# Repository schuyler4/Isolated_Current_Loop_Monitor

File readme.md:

<h1> Isolated Current Loop Monitor </h1>

<center>

</center>

<p> This circuit monitors the state of a switch (or many switches in series) with an isolated signal. This is the only way to truly monitor the state of a switch without any
information about the signal that the switch is switching. 
</p>
<h3>Inputs</h3>
<ul>
<li>12V Power</li>
<li>Switch Loop (Connect each end to switch connector)</li>
</ul>
<h3>Output</h3>
The output is open collector with a 10k pull up resistor. When the 
switch loop is closed, the open collector pulls low, and when the switch
is open, it releases.

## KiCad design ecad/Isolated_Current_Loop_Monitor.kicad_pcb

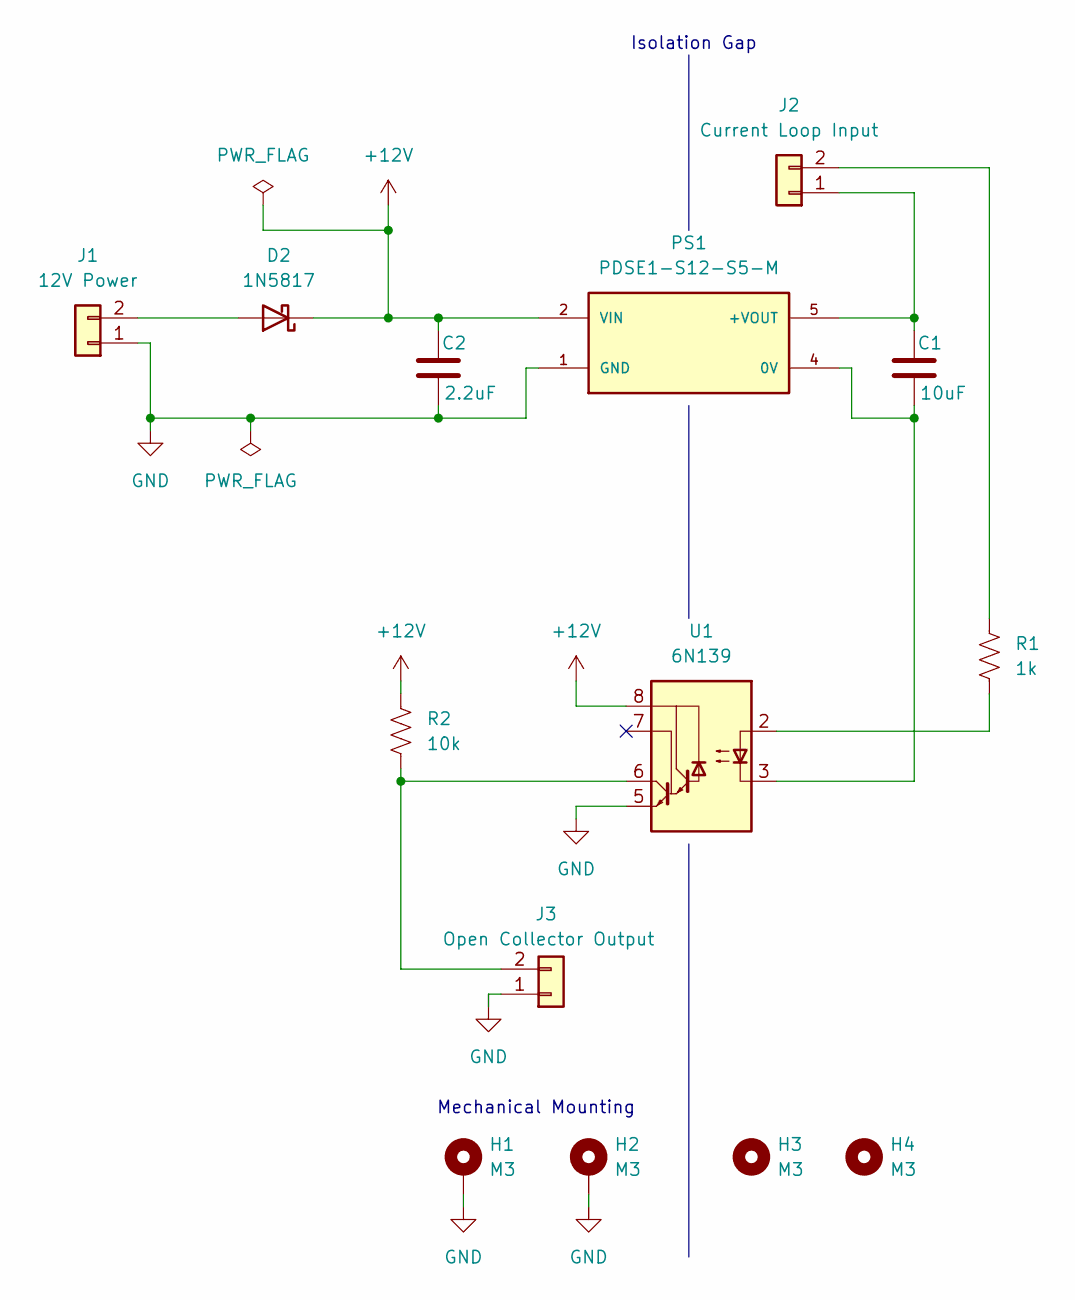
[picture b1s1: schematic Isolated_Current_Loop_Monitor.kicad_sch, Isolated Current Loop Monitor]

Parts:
C1: 10uF; C_Disc_D6.0mm_W2.5mm_P5.00mm; Part # FG20X7R1H106KRT06; Digikey Part # 445-173297-1-ND
C2: 2.2uF; C_Disc_D6.0mm_W2.5mm_P5.00mm; Part # RDER71H225K2M1H03A; Digikey Part # 490-9164-1-ND
D2: 1N5817; D_DO-41_SOD81_P10.16mm_Horizontal; Part # 1N5817; Digikey Part # 497-4547-1-ND
H1, H2: M3; MountingHole_3.2mm_M3_Pad_Via
H3, H4: M3; MountingHole_3.2mm_M3
J1: 12V Power; MOLEX_2125280200; Part # 2125280200; Digikey Part # 900-2125280200-ND
J2: Current Loop Input; MOLEX_2125280200; Part # 2125280200; Digikey Part # 900-2125280200-ND
J3: Open Collector Output; MOLEX_2125280200; Part # 2125280200; Digikey Part # 900-2125280200-ND
PS1: PDSE1-S12-S5-M; CONV_PDSE1-S12-S5-M; PARTREV 1.0; Digikey Part # 102-PDSE1-S12-S5-M-ND
R1: 1k; R_Axial_DIN0207_L6.3mm_D2.5mm_P7.62mm_Horizontal; Part # CFF14JT1K00; Digikey Part # 738-CFF14JT1K00CT-ND
R2: 10k; R_Axial_DIN0207_L6.3mm_D2.5mm_P7.62mm_Horizontal; Part # CF14JT10K0; Digikey Part # CF14JT10K0CT-ND
U1: 6N139; DIP-8_W7.62mm; Part # 6N139-ND; Digikey Part # 6N139-ND

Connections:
+12V: C2.1, D2.1 (K), PS1.2 (VIN), R2.1, U1.8 (VCC)
GND: C2.2, H1.1, H2.1, J1.1, J3.1, PS1.1 (GND), U1.5 (GND)
unnamed: D2.2 (A), J1.2
unnamed: C1.1, J2.1, PS1.5 (+VOUT)
unnamed: J2.2, R1.1
unnamed: J3.2, R2.2, U1.6 (VO2)
unnamed: C1.2, PS1.4 (0V), U1.3 (C2)
unnamed: R1.2, U1.2 (C1)

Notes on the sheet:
Isolation Gap
Mechanical Mounting

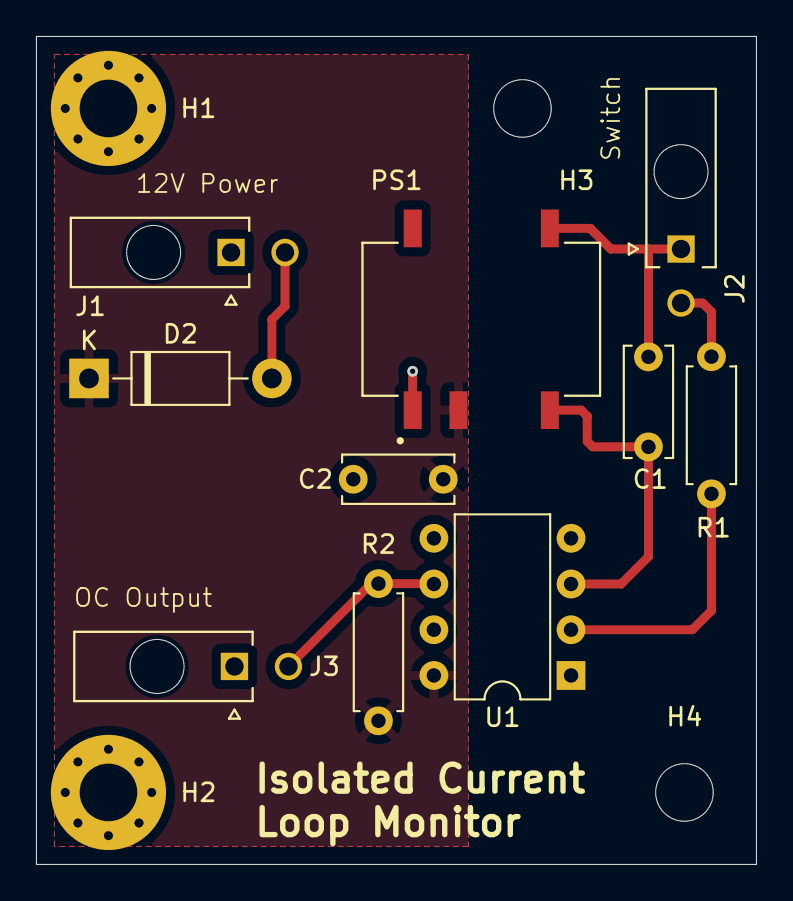
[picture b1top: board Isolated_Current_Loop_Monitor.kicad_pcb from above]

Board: 2 copper layers, 40.0 x 46.0 mm, 14 parts (0 on the bottom side), 8 nets.

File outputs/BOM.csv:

Reference,Value,Qty,Part #,Digikey Part #,Unit Price
C1,10uF,1,FG20X7R1H106KRT06,445-173297-1-ND,1.29
C2,2.2uF,1,RDER71H225K2M1H03A,490-9164-1-ND,0.74
D2,1N5817,1,1N5817,497-4547-1-ND,0.42
J1,12V Power,1,2125280200,900-2125280200-ND,2.13
J2,Current Loop Input,1,2125280200,900-2125280200-ND,2.13
J3,Open Collector Output,1,2125280200,900-2125280200-ND,2.13
PS1,PDSE1-S12-S5-M,1,PDSE1-S12-S5-M,102-PDSE1-S12-S5-M-ND,3.45
R1,1k,1,CFF14JT1K00,738-CFF14JT1K00CT-ND,0.12
R2,10k,1,CF14JT10K0,CF14JT10K0CT-ND,0.1
U1,6N139,1,6N139-ND,6N139-ND,1.79
total:,,,,,14.3

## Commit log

2024-03-17 license
2024-03-17 purge
